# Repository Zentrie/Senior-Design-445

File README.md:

# 445

An autonomous food container dispenser machine. 

Team Members:

Ariocie Liang (arliang2), John Kim (jaehank2), Henry Guan (henryg3)

## PROBLEM

Good2Go (G2G) containers are used all throughout dining halls for individuals wanting to take their food to go. The program allows you to trade in an old container for a token, where that token can then be used to trade for a new container. This is a hassle for both parties that handle the entire process. It's very redundant and can be streamlined/improved with mechanical assistance.

## SOLUTION

Our solution involves a token/food container swapping machine that serves 2 main functions:

Have a G2G token, that upon deposit, returns a clean container.
Accept a used container, returning a G2G token or a clean container.
The goal here is to make the process semi-autonomous by removing 2 stages of interaction, as well as speeding up the entire process by doing so.

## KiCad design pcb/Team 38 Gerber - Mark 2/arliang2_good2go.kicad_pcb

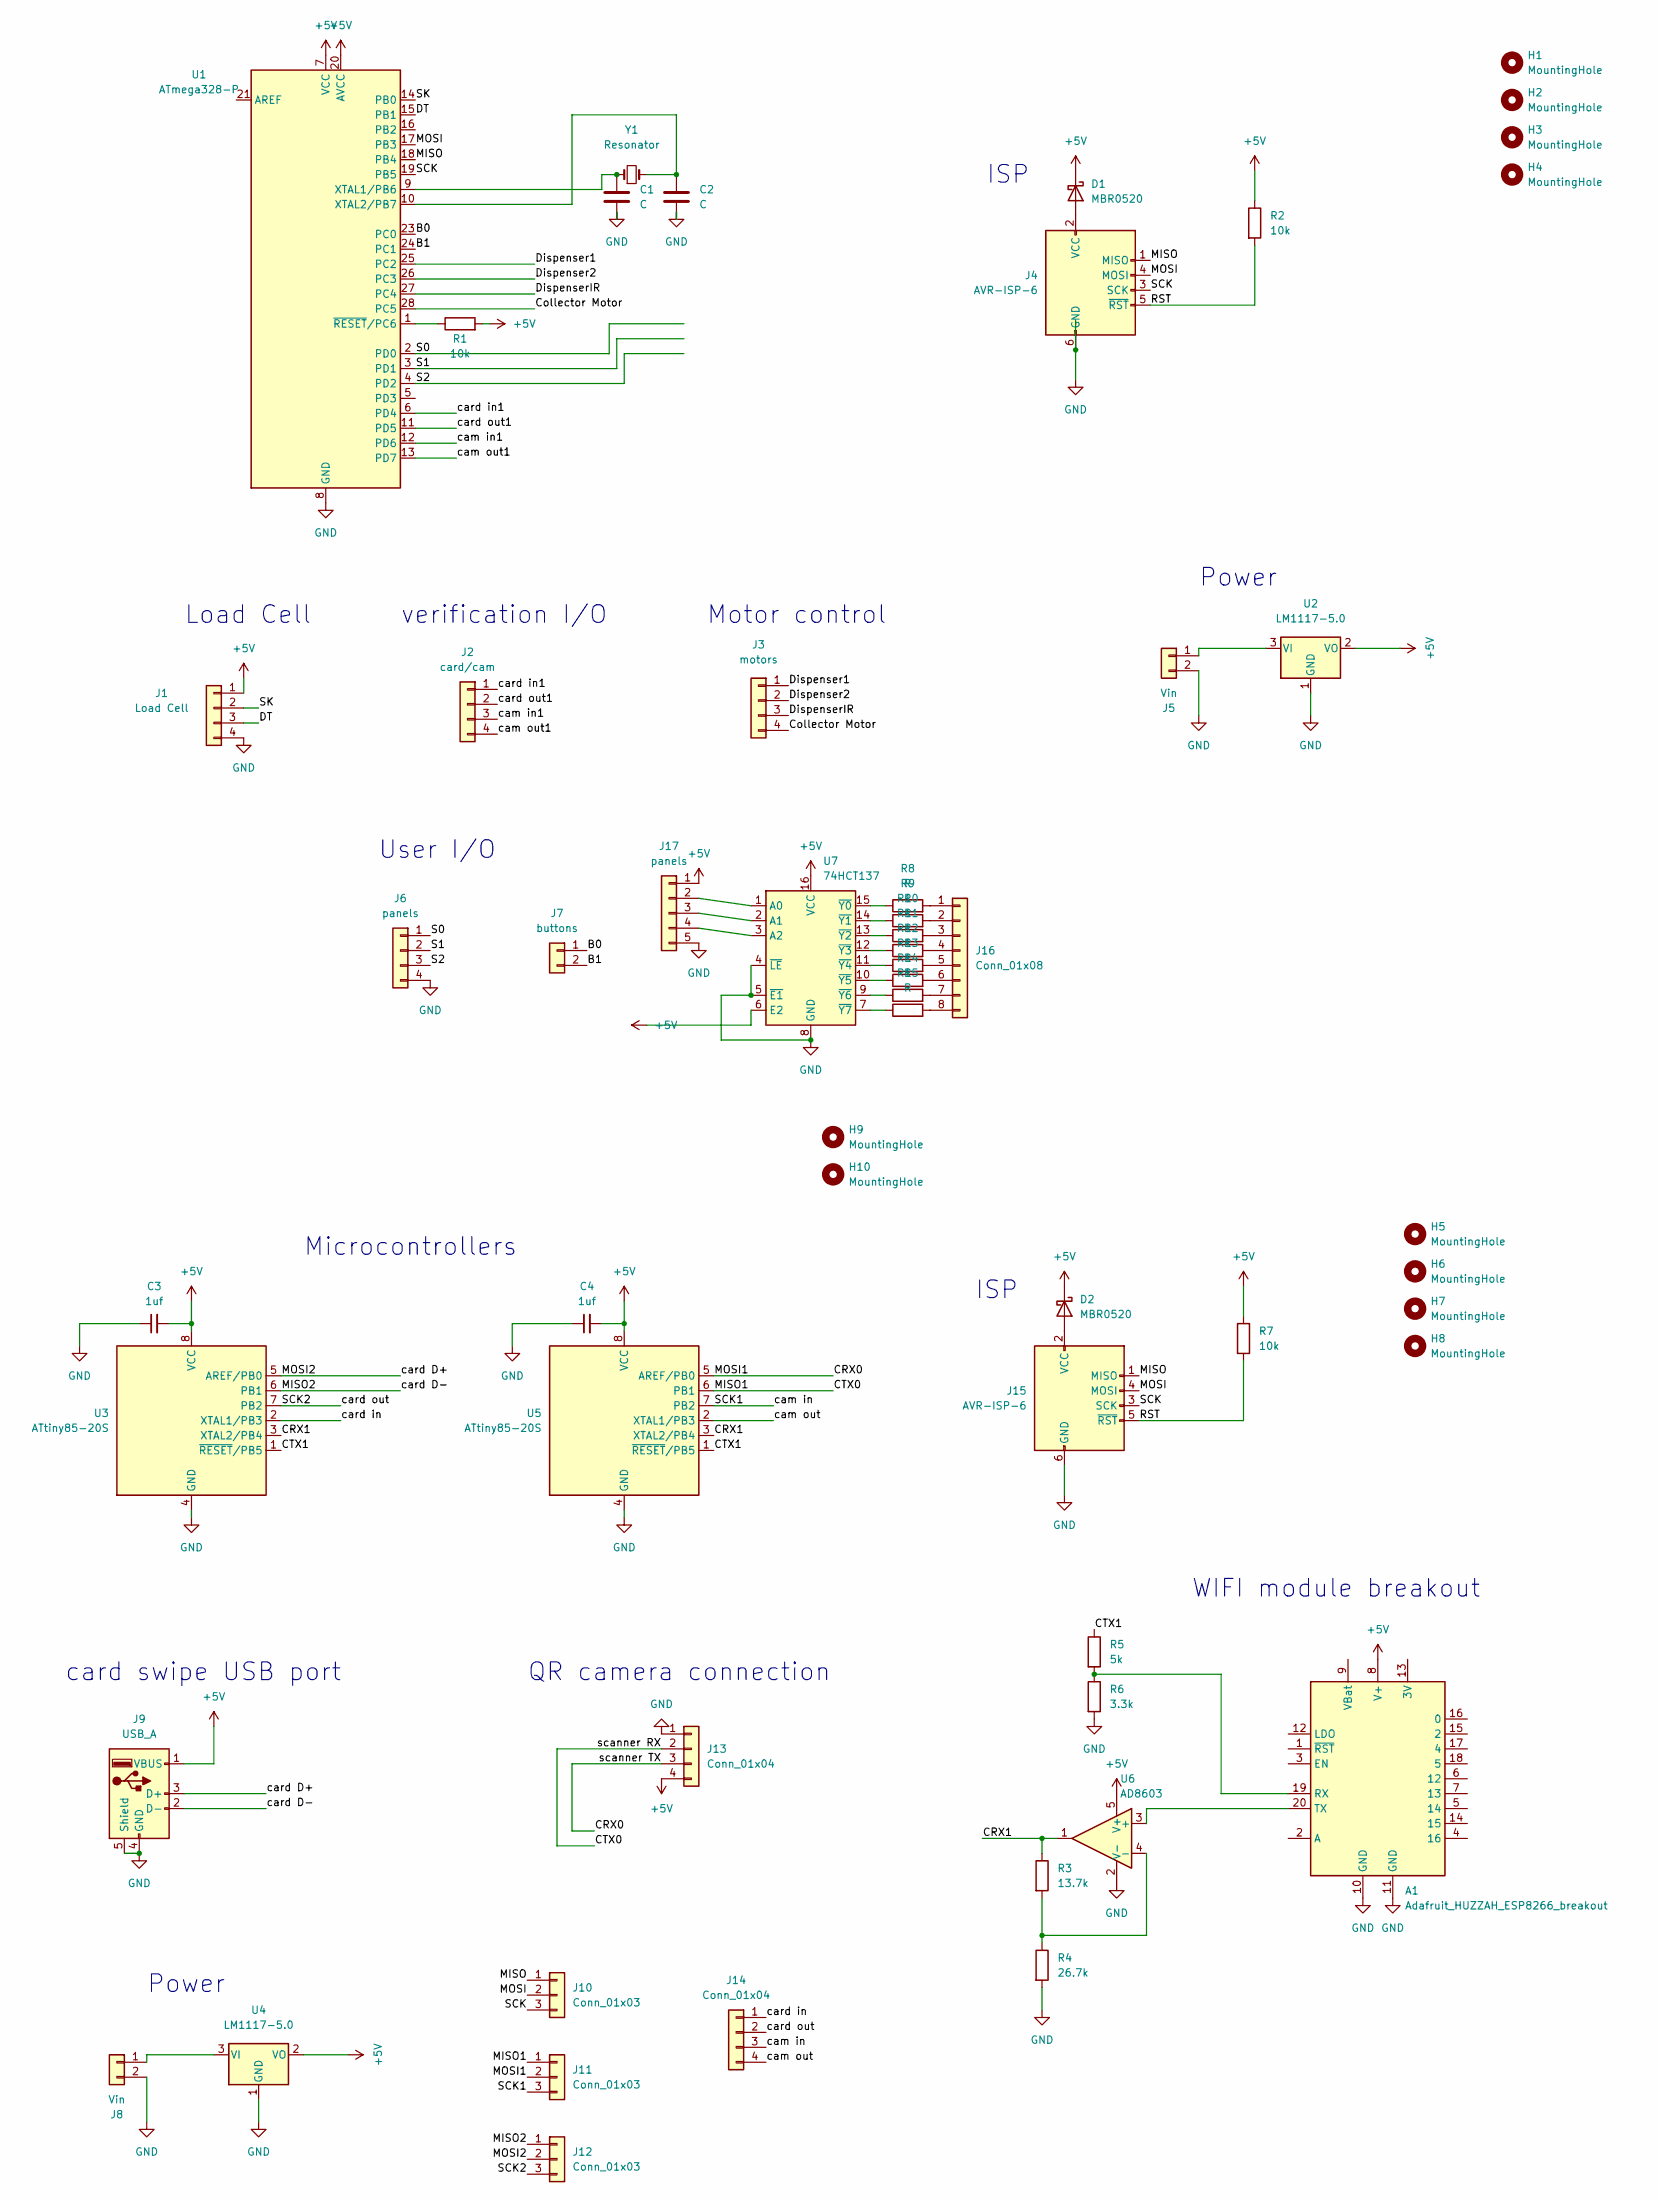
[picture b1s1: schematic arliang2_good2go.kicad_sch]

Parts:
A1: Adafruit_HUZZAH_ESP8266_breakout; Adafruit_HUZZAH_ESP8266_breakout_WithMountingHoles
C1, C2: C; C_0805_2012Metric_Pad1.18x1.45mm_HandSolder
C3, C4: 1uf; C_0805_2012Metric_Pad1.18x1.45mm_HandSolder
D1, D2: MBR0520; D_SOD-123
H1, H2, H3, H4, H5, H6, H7, H8, H9, H10: MountingHole; MountingHole_3.2mm_M3
J1: Load Cell; Molex_KK-254_AE-6410-04A_1x04_P2.54mm_Vertical
J2: card/cam; Molex_KK-254_AE-6410-04A_1x04_P2.54mm_Vertical
J3: motors; Molex_KK-254_AE-6410-04A_1x04_P2.54mm_Vertical
J4, J15: AVR-ISP-6; IDC-Header_2x03_P2.54mm_Vertical
J5, J8: Vin; Molex_KK-254_AE-6410-02A_1x02_P2.54mm_Vertical
J6: panels; Molex_KK-254_AE-6410-03A_1x03_P2.54mm_Vertical
J7: buttons; Molex_KK-254_AE-6410-02A_1x02_P2.54mm_Vertical
J9: USB_A; USB_A_Stewart_SS-52100-001_Horizontal
J10, J11, J12: Conn_01x03; Molex_KK-254_AE-6410-03A_1x03_P2.54mm_Vertical
J13, J14: Conn_01x04; Molex_KK-254_AE-6410-04A_1x04_P2.54mm_Vertical
J16: Conn_01x08; Molex_KK-254_AE-6410-08A_1x08_P2.54mm_Vertical
J17: panels; Molex_KK-254_AE-6410-05A_1x05_P2.54mm_Vertical
R1, R2: 10k; R_0805_2012Metric_Pad1.20x1.40mm_HandSolder
R3: 13.7k; R_0805_2012Metric_Pad1.20x1.40mm_HandSolder
R4: 26.7k; R_0805_2012Metric_Pad1.20x1.40mm_HandSolder
R5: 5k; R_0805_2012Metric_Pad1.20x1.40mm_HandSolder
R6: 3.3k; R_0805_2012Metric_Pad1.20x1.40mm_HandSolder
R7: 10k; C_0805_2012Metric_Pad1.18x1.45mm_HandSolder
R8, R9, R10, R11, R12, R13, R14, R15: R; R_0805_2012Metric_Pad1.20x1.40mm_HandSolder
U1: ATmega328-P; DIP-28_W7.62mm_Socket
U2, U4: LM1117-5.0; SOT-223
U3, U5: ATtiny85-20S; SOIC-8W_5.3x5.3mm_P1.27mm
U6: AD8603; TSOT-23-5
U7: 74HCT137; DIP-16_W7.62mm
Y1: Resonator; Crystal_HC49-U_Vertical

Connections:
+5V: A1.8 (V+), C3.2, C4.2, D1.1 (K), D2.1 (K), J1.1, J9.1 (VBUS), J13.4, J17.1, R1.2, R2.1, R7.1, U1.7 (VCC), U1.20 (AVCC), U2.2 (VO), U3.8 (VCC), U4.2 (VO), U5.8 (VCC), U6.5 (V+), U7.6 (E2), U7.16 (VCC)
/B0: J7.1, U1.23 (PC0)
/B1: J7.2, U1.24 (PC1)
/CRX0: J11.2, J13.3, U5.5 (AREF/PB0)
/CRX1: R3.1, U3.3 (XTAL2/PB4), U5.3 (XTAL2/PB4), U6.1
/CTX0: J11.1, J13.2, U5.6 (PB1)
/CTX1: R5.1, U3.1 (~RESET/PB5), U5.1 (~RESET/PB5)
/Collector Motor: J3.4, U1.28 (PC5)
/DT: J1.3, U1.15 (PB1)
/Dispenser1: J3.1, U1.25 (PC2)
/Dispenser2: J3.2, U1.26 (PC3)
/DispenserIR: J3.3, U1.27 (PC4)
/MISO: J4.1 (MISO), J10.1, J15.1 (MISO), U1.18 (PB4)
/MISO2: J9.2 (D-), J12.1, U3.6 (PB1)
/MOSI: J4.4 (MOSI), J10.2, J15.4 (MOSI), U1.17 (PB3)
/MOSI2: J9.3 (D+), J12.2, U3.5 (AREF/PB0)
/RST: J4.5 (~RST), J15.5 (~RST), R2.2, R7.2
/S0: J6.1, U1.2 (PD0)
/S1: J6.2, U1.3 (PD1)
/S2: J6.3, U1.4 (PD2)
/SCK: J4.3 (SCK), J10.3, J15.3 (SCK), U1.19 (PB5)
/SCK1: J11.3, J14.3, U5.7 (PB2)
/SCK2: J12.3, J14.2, U3.7 (PB2)
/SK: J1.2, U1.14 (PB0)
/cam in1: J2.3, U1.12 (PD6)
/cam out: J14.4, U5.2 (XTAL1/PB3)
/cam out1: J2.4, U1.13 (PD7)
/card in: J14.1, U3.2 (XTAL1/PB3)
/card in1: J2.1, U1.6 (PD4)
/card out1: J2.2, U1.11 (PD5)
GND: A1.10 (GND), A1.11 (GND), C1.2, C2.2, C3.1, C4.1, J1.4, J4.6 (GND), J5.2, J6.4, J8.2, J9.4 (GND), J9.5 (Shield), J13.1, J15.6 (GND), J17.5, R4.2, R6.2, U1.8 (GND), U1.22 (GND), U2.1 (GND), U3.4 (GND), U4.1 (GND), U5.4 (GND), U6.2 (V-), U7.4 (~LE), U7.5 (~E1), U7.8 (GND)
unnamed: A1.19 (RX), R5.2, R6.1
unnamed: A1.20 (TX), U6.3 (+)
unnamed: C1.1, U1.9 (XTAL1/PB6), Y1.1
unnamed: C2.1, U1.10 (XTAL2/PB7), Y1.2
unnamed: D1.2 (A), J4.2 (VCC)
unnamed: D2.2 (A), J15.2 (VCC)
unnamed: J5.1, U2.3 (VI)
unnamed: J8.1, U4.3 (VI)
unnamed: J16.1, R8.2
unnamed: J16.2, R9.2
unnamed: J16.3, R10.2
unnamed: J16.4, R11.2
unnamed: J16.5, R12.2
unnamed: J16.6, R13.2
unnamed: J16.7, R14.2
unnamed: J16.8, R15.2
unnamed: J17.2, U7.1 (A0)
unnamed: J17.3, U7.2 (A1)
unnamed: J17.4, U7.3 (A2)
unnamed: R1.1, U1.1 (~RESET/PC6)
unnamed: R3.2, R4.1, U6.4 (-)
unnamed: R8.1, U7.15 (~Y0)
unnamed: R9.1, U7.14 (~Y1)
unnamed: R10.1, U7.13 (~Y2)
unnamed: R11.1, U7.12 (~Y3)
unnamed: R12.1, U7.11 (~Y4)
unnamed: R13.1, U7.10 (~Y5)
unnamed: R14.1, U7.9 (~Y6)
unnamed: R15.1, U7.7 (~Y7)

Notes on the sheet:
Power
card swipe USB port
WIFI module breakout
QR camera connection
verification I/O
Motor control
User I/O
Microcontrollers
ISP
Load Cell

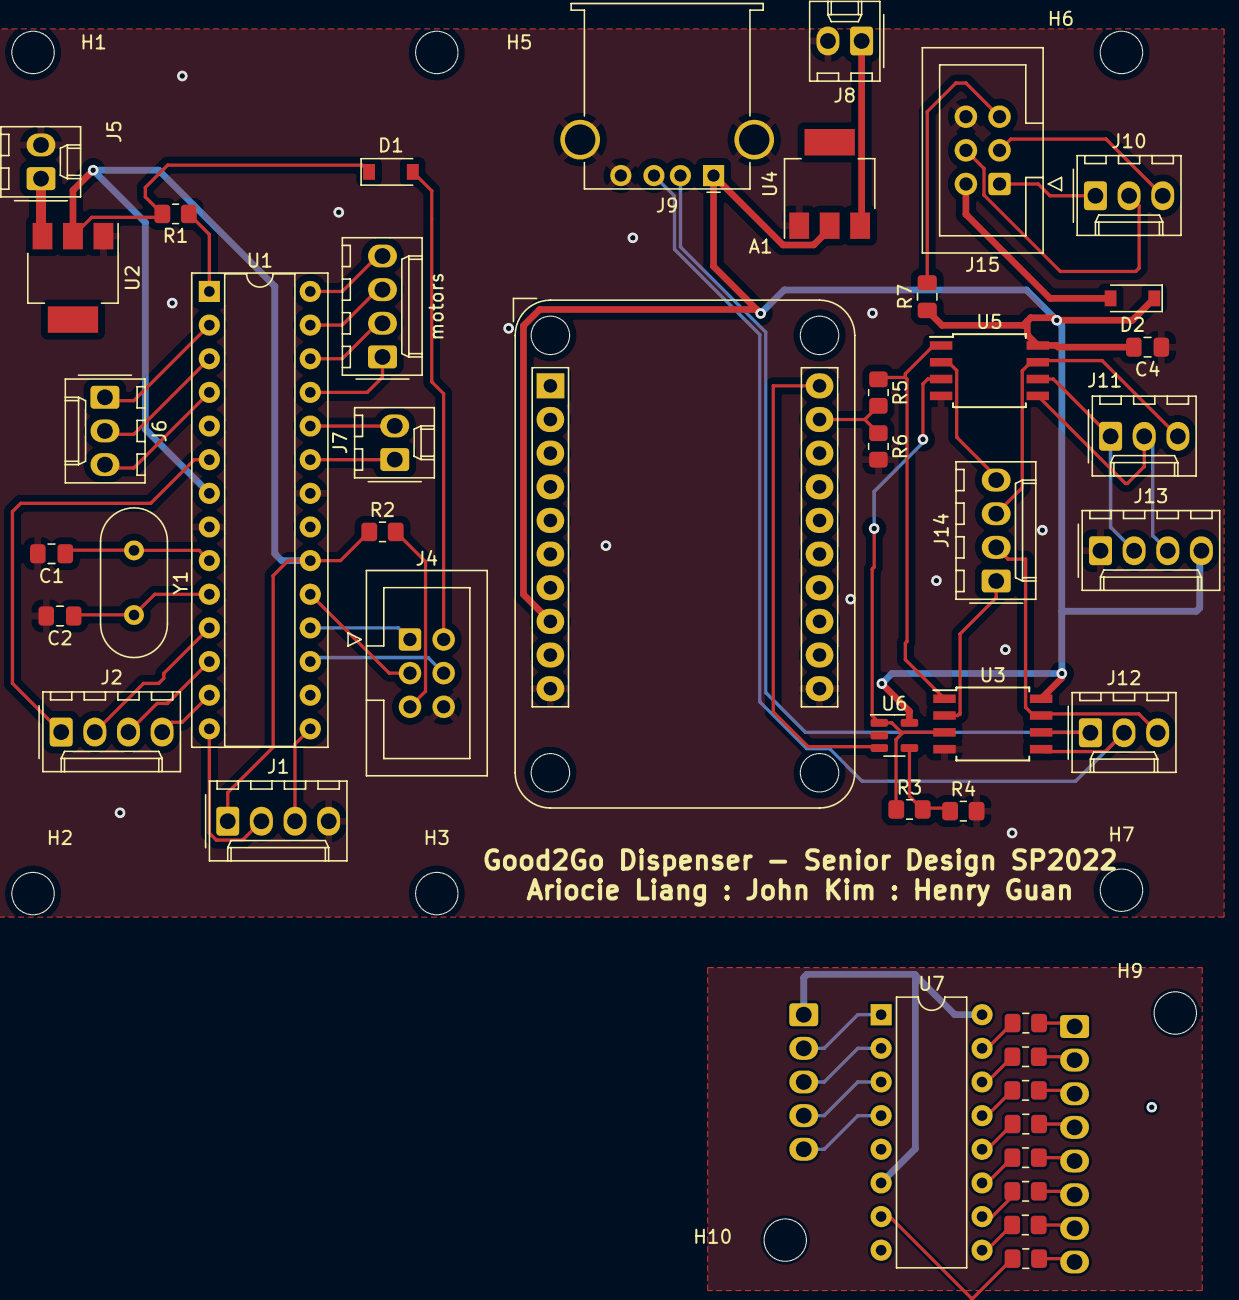
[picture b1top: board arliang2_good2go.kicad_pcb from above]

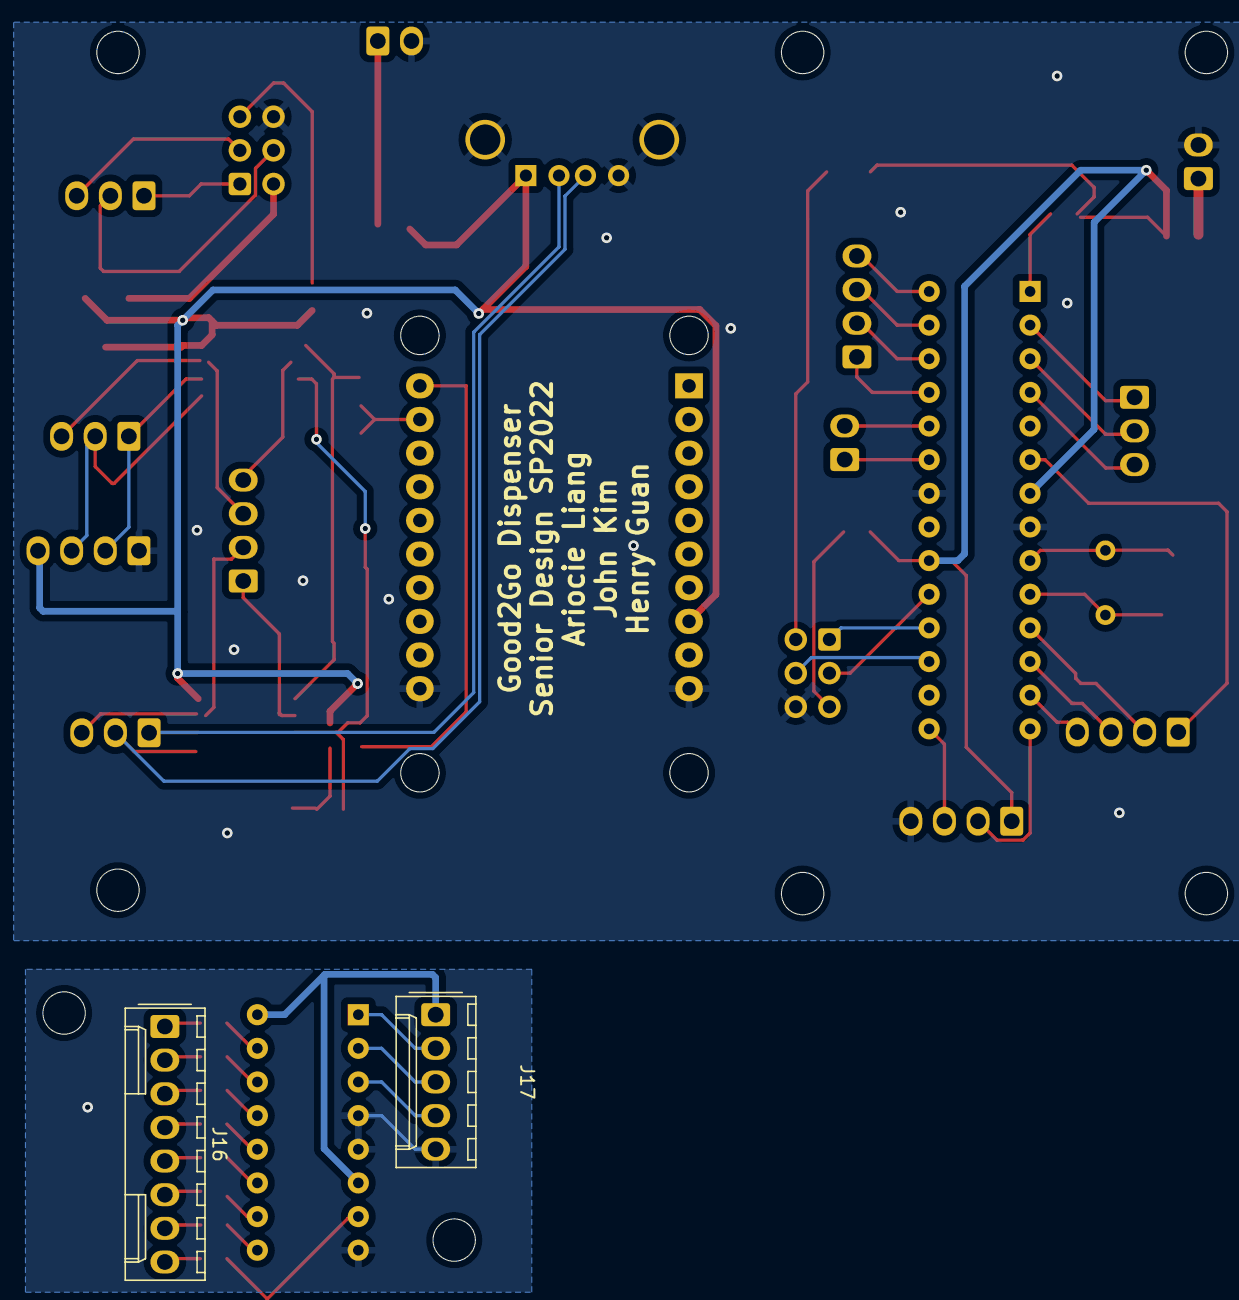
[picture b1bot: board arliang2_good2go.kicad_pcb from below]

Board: 2 copper layers, 54 parts (2 on the bottom side), 60 nets.

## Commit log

2022-02-08 added RFA from Web Board
2022-02-08 connection established, first steps of organization
2022-02-28 added design doc
2022-03-28 testing
2022-03-28 testing 2
2022-03-28 PCB first draft - SMD
2022-03-29 updating README
2022-04-12 Create log
2022-04-19 adding notebook section
2022-05-04 adding notebook
2022-05-04 fixing formatting
2022-05-04 minor format issues
2022-05-04 final touch
2022-05-04 final touches
2022-05-04 final
2022-05-04 updating repo
2022-05-04 deleting dupe
2022-05-04 adding notebook for john
2022-05-04 reorganizing structure on git
2022-05-04 adding images
2022-05-05 final update
2022-05-05 test
2022-05-05 Final notebook update
